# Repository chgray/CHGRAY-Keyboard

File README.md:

https://github.com/freerouting/freerouting

# QMK Tips
./bin/qmk info -km default -kb handwired/ckey

# Graphical view of the keyboard
./bin/qmk info -kb handwired/ckey -l

# Parts
https://kbdfans.com/

# VIA
keyboard layout editor - http://www.keyboard-layout-editor.com/

https://caniusevia.com/docs/specification/

https://get.vial.today/

#QMK PR reqs
The general guide to send PRs to QMK is https://docs.qmk.fm/#/contributing; there is also the PR checklist https://docs.qmk.fm/#/pr_checklist th

qmk c2json -km default -kb handwired/ckey -o foo.json ./keyboards/handwired/ckey/keymaps/default/keymap.c

# To Make the keyplate
	1. in notepad replace Eco.User1 with Edge.Cuts
	2. from pcbnew export the Edge.Cuts layer as a DXF
	3. import this back into pcbnew
	4. Delete all the active components and then manually patch up things

# Parts 
Purchased LED's ffrom https://www.adafruit.com/product/4960

# KiCad
 - to make the file load pcbnew and then do File->Fabrication Outputs.  save a .pos file {CSV, millimeters, seperate files for front/back} -> Generate Position File.  (chgray-keyboard-top-pos.csv)
	A) Change Ref to Designator
	B) Rot to Rotation
	C) Side to Layer
	D) PoxX to "Mid X"
	E) PosY to "Mid Y"
 
 - to make the BOM load eeschema and then do the button ("generate bill of material") BOM -> bom2csv
     you're looking for chgray-keyboard.csv
	A) Change Reference to "Designator"
	B) Change Datasheet to "JLCPCB Part #"
	C) Value to Comment

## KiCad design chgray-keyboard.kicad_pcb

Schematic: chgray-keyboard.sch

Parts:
J1: Conn_01x07_Female; PinHeader_1x08_P2.54mm_Vertical

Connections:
COL12: J1.3; also elsewhere on the board
COL13: J1.4; also elsewhere on the board
LED_DATA: J1.2; also elsewhere on the board
LED_OUT: J1.8; also elsewhere on the board
RESET: J1.6; also elsewhere on the board
ROW0: J1.5; also elsewhere on the board

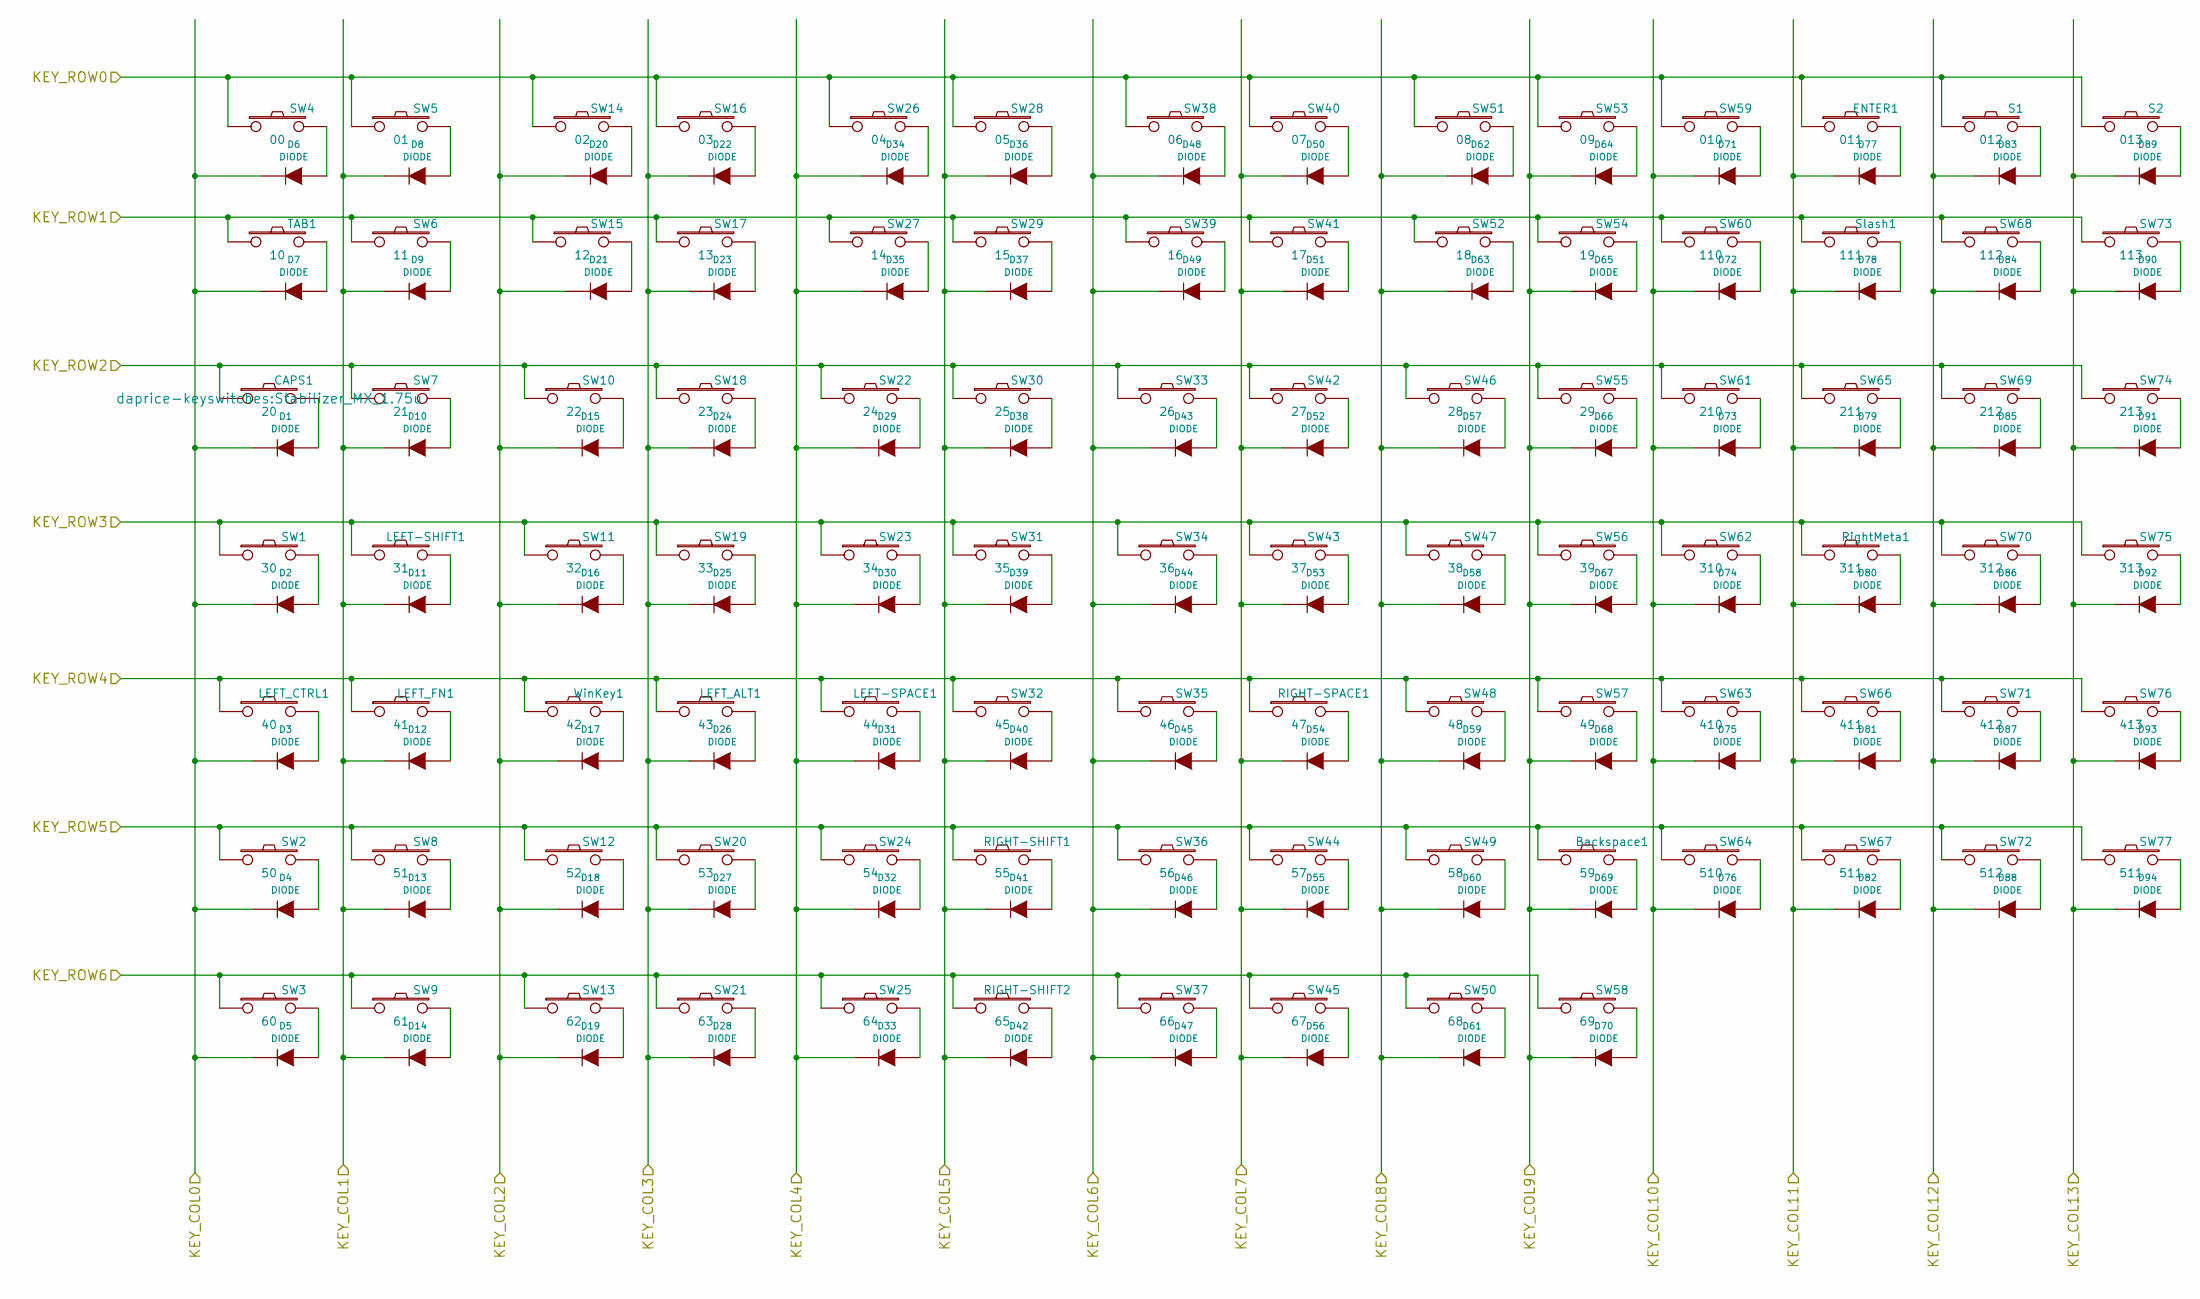
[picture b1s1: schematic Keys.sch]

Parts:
Backspace1: 59; Stabilizer_MX_2u
CAPS1: 20; Stabilizer_MX_1.75u
D1, D2, D3, D4, D5, D6, D7, D8, D9, D10, D11, D12, D13, D14, D15, D16, D17, D18, D19, D20, D21, D22, D23, D24, D25, D26, D27, D28, D29, D30, D31, D32, D33, D34, D35, D36, D37, D38, D39, D40, D41, D42, D43, D44, D45, D46, D47, D48, D49, D50, D51, D52, D53, D54, D55, D56, D57, D58, D59, D60, D61, D62, D63, D64, D65, D66, D67, D68, D69, D70, D71, D72, D73, D74, D75, D76, D77, D78, D79, D80, D81, D82, D83, D84, D85, D86, D87, D88, D89, D90, D91, D92, D93, D94: DIODE; D_SOD-123FL
ENTER1: 011; Stabilizer_MX_2.25u
LEFT-SHIFT1: 31; Stabilizer_MX_2.25u
LEFT-SPACE1: 44; Kailh_socket_MX
LEFT_ALT1: 43; Kailh_socket_MX
LEFT_CTRL1: 40; Stabilizer_MX_1.25u
LEFT_FN1: 41; Stabilizer_MX_1.25u
RIGHT-SHIFT1: 55; Stabilizer_MX_2.75u
RIGHT-SHIFT2: 65; Kailh_socket_MX
RIGHT-SPACE1: 47; Stabilizer_MX_1.25u
RightMeta1: 311; Stabilizer_MX_1.25u
S1: 012; Kailh_socket_MX
S2: 013; Kailh_socket_MX
SW1: 30; Kailh_socket_MX
SW2: 50; Kailh_socket_MX
SW3: 60; Kailh_socket_MX
SW4: 00; Kailh_socket_MX
SW5: 01; Kailh_socket_MX
SW6: 11; Kailh_socket_MX
SW7: 21; Kailh_socket_MX
SW8: 51; Kailh_socket_MX
SW9: 61; Kailh_socket_MX
SW10: 22; Kailh_socket_MX
SW11: 32; Kailh_socket_MX
SW12: 52; Kailh_socket_MX
SW13: 62; Kailh_socket_MX
SW14: 02; Kailh_socket_MX
SW15: 12; Kailh_socket_MX
SW16: 03; Kailh_socket_MX
SW17: 13; Kailh_socket_MX
SW18: 23; Kailh_socket_MX
SW19: 33; Kailh_socket_MX
SW20: 53; Kailh_socket_MX
SW21: 63; Kailh_socket_MX
SW22: 24; Kailh_socket_MX
SW23: 34; Kailh_socket_MX
SW24: 54; Kailh_socket_MX
SW25: 64; Kailh_socket_MX
SW26: 04; Kailh_socket_MX
SW27: 14; Kailh_socket_MX
SW28: 05; Kailh_socket_MX
SW29: 15; Kailh_socket_MX
SW30: 25; Kailh_socket_MX
SW31: 35; Kailh_socket_MX
SW32: 45; Kailh_socket_MX
SW33: 26; Kailh_socket_MX
SW34: 36; Kailh_socket_MX
SW35: 46; Kailh_socket_MX
SW36: 56; Kailh_socket_MX
SW37: 66; Kailh_socket_MX
SW38: 06; Kailh_socket_MX
SW39: 16; Kailh_socket_MX
SW40: 07; Kailh_socket_MX
SW41: 17; Kailh_socket_MX
SW42: 27; Kailh_socket_MX
SW43: 37; Kailh_socket_MX
SW44: 57; Kailh_socket_MX
SW45: 67; Kailh_socket_MX
SW46: 28; Kailh_socket_MX
SW47: 38; Kailh_socket_MX
SW48: 48; Stabilizer_MX_1.25u
SW49: 58; Kailh_socket_MX
SW50: 68; Kailh_socket_MX
SW51: 08; Kailh_socket_MX
SW52: 18; Kailh_socket_MX
SW53: 09; Kailh_socket_MX
SW54: 19; Kailh_socket_MX
SW55: 29; Kailh_socket_MX
SW56: 39; Kailh_socket_MX
SW57: 49; CHERRY_PCB_625H
SW58: 69; Stabilizer_MX_1.25u
SW59: 010; Kailh_socket_MX
SW60: 110; Kailh_socket_MX
SW61: 210; Kailh_socket_MX
SW62: 310; Kailh_socket_MX
SW63: 410; Kailh_socket_MX
SW64: 510; Kailh_socket_MX
SW65: 211; Kailh_socket_MX
SW66: 411; Kailh_socket_MX
SW67, SW77: 511; Kailh_socket_MX
SW68: 112; Kailh_socket_MX
SW69: 212; Kailh_socket_MX
SW70: 312; Kailh_socket_MX
SW71: 412; Kailh_socket_MX
SW72: 512; Kailh_socket_MX
SW73: 113; Kailh_socket_MX
SW74: 213; Kailh_socket_MX
SW75: 313; Kailh_socket_MX
SW76: 413; Kailh_socket_MX
Slash1: 111; Stabilizer_MX_1.5u
TAB1: 10; Stabilizer_MX_1.5u
WinKey1: 42; Stabilizer_MX_1.25u

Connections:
COL0: D1.2 (K), D2.2 (K), D3.2 (K), D4.2 (K), D5.2 (K), D6.2 (K), D7.2 (K); also elsewhere on the board
COL1: D8.2 (K), D9.2 (K), D10.2 (K), D11.2 (K), D12.2 (K), D13.2 (K), D14.2 (K); also elsewhere on the board
COL2: D15.2 (K), D16.2 (K), D17.2 (K), D18.2 (K), D19.2 (K), D20.2 (K), D21.2 (K); also elsewhere on the board
COL3: D22.2 (K), D23.2 (K), D24.2 (K), D25.2 (K), D26.2 (K), D27.2 (K), D28.2 (K); also elsewhere on the board
COL4: D29.2 (K), D30.2 (K), D31.2 (K), D32.2 (K), D33.2 (K), D34.2 (K), D35.2 (K); also elsewhere on the board
COL5: D36.2 (K), D37.2 (K), D38.2 (K), D39.2 (K), D40.2 (K), D41.2 (K), D42.2 (K); also elsewhere on the board
COL6: D43.2 (K), D44.2 (K), D45.2 (K), D46.2 (K), D47.2 (K), D48.2 (K), D49.2 (K); also elsewhere on the board
COL7: D50.2 (K), D51.2 (K), D52.2 (K), D53.2 (K), D54.2 (K), D55.2 (K), D56.2 (K); also elsewhere on the board
COL8: D57.2 (K), D58.2 (K), D59.2 (K), D60.2 (K), D61.2 (K), D62.2 (K), D63.2 (K); also elsewhere on the board
COL9: D64.2 (K), D65.2 (K), D66.2 (K), D67.2 (K), D68.2 (K), D69.2 (K), D70.2 (K); also elsewhere on the board
COL10: D71.2 (K), D72.2 (K), D73.2 (K), D74.2 (K), D75.2 (K), D76.2 (K); also elsewhere on the board
COL11: D77.2 (K), D78.2 (K), D79.2 (K), D80.2 (K), D81.2 (K), D82.2 (K); also elsewhere on the board
COL12: D83.2 (K), D84.2 (K), D85.2 (K), D86.2 (K), D87.2 (K), D88.2 (K); also elsewhere on the board
COL13: D89.2 (K), D90.2 (K), D91.2 (K), D92.2 (K), D93.2 (K), D94.2 (K); also elsewhere on the board
unnamed: Backspace1.2, D69.1 (A)
unnamed: CAPS1.2, D1.1 (A)
unnamed: D2.1 (A), SW1.2
unnamed: D3.1 (A), LEFT_CTRL1.2
unnamed: D4.1 (A), SW2.2
unnamed: D5.1 (A), SW3.2
unnamed: D6.1 (A), SW4.2
unnamed: D7.1 (A), TAB1.2
unnamed: D8.1 (A), SW5.2
unnamed: D9.1 (A), SW6.2
unnamed: D10.1 (A), SW7.2
unnamed: D11.1 (A), LEFT-SHIFT1.2
unnamed: D12.1 (A), LEFT_FN1.2
unnamed: D13.1 (A), SW8.2
unnamed: D14.1 (A), SW9.2
unnamed: D15.1 (A), SW10.2
unnamed: D16.1 (A), SW11.2
unnamed: D17.1 (A), WinKey1.2
unnamed: D18.1 (A), SW12.2
unnamed: D19.1 (A), SW13.2
unnamed: D20.1 (A), SW14.2
unnamed: D21.1 (A), SW15.2
unnamed: D22.1 (A), SW16.2
unnamed: D23.1 (A), SW17.2
unnamed: D24.1 (A), SW18.2
unnamed: D25.1 (A), SW19.2
unnamed: D26.1 (A), LEFT_ALT1.2
unnamed: D27.1 (A), SW20.2
unnamed: D28.1 (A), SW21.2
unnamed: D29.1 (A), SW22.2
unnamed: D30.1 (A), SW23.2
unnamed: D31.1 (A), LEFT-SPACE1.2
unnamed: D32.1 (A), SW24.2
unnamed: D33.1 (A), SW25.2
unnamed: D34.1 (A), SW26.2
unnamed: D35.1 (A), SW27.2
unnamed: D36.1 (A), SW28.2
unnamed: D37.1 (A), SW29.2
unnamed: D38.1 (A), SW30.2
unnamed: D39.1 (A), SW31.2
unnamed: D40.1 (A), SW32.2
unnamed: D41.1 (A), RIGHT-SHIFT1.2
unnamed: D42.1 (A), RIGHT-SHIFT2.2
unnamed: D43.1 (A), SW33.2
unnamed: D44.1 (A), SW34.2
unnamed: D45.1 (A), SW35.2
unnamed: D46.1 (A), SW36.2
unnamed: D47.1 (A), SW37.2
unnamed: D48.1 (A), SW38.2
unnamed: D49.1 (A), SW39.2
unnamed: D50.1 (A), SW40.2
unnamed: D51.1 (A), SW41.2
unnamed: D52.1 (A), SW42.2
unnamed: D53.1 (A), SW43.2
unnamed: D54.1 (A), RIGHT-SPACE1.2
unnamed: D55.1 (A), SW44.2
unnamed: D56.1 (A), SW45.2
unnamed: D57.1 (A), SW46.2
unnamed: D58.1 (A), SW47.2
unnamed: D59.1 (A), SW48.2
unnamed: D60.1 (A), SW49.2
unnamed: D61.1 (A), SW50.2
unnamed: D62.1 (A), SW51.2
unnamed: D63.1 (A), SW52.2
unnamed: D64.1 (A), SW53.2
unnamed: D65.1 (A), SW54.2
unnamed: D66.1 (A), SW55.2
unnamed: D67.1 (A), SW56.2
unnamed: D68.1 (A), SW57.2
unnamed: D70.1 (A), SW58.2
unnamed: D71.1 (A), SW59.2
unnamed: D72.1 (A), SW60.2
unnamed: D73.1 (A), SW61.2
unnamed: D74.1 (A), SW62.2
unnamed: D75.1 (A), SW63.2
unnamed: D76.1 (A), SW64.2
unnamed: D77.1 (A), ENTER1.2
unnamed: D78.1 (A), Slash1.2
unnamed: D79.1 (A), SW65.2
unnamed: D80.1 (A), RightMeta1.2
unnamed: D81.1 (A), SW66.2
unnamed: D82.1 (A), SW67.2
unnamed: D83.1 (A), S1.2
unnamed: D84.1 (A), SW68.2
unnamed: D85.1 (A), SW69.2
unnamed: D86.1 (A), SW70.2
unnamed: D87.1 (A), SW71.2
unnamed: D88.1 (A), SW72.2
unnamed: D89.1 (A), S2.2
unnamed: D90.1 (A), SW73.2
unnamed: D91.1 (A), SW74.2
unnamed: D92.1 (A), SW75.2
unnamed: D93.1 (A), SW76.2
unnamed: D94.1 (A), SW77.2
ROW0: ENTER1.1, S1.1, S2.1, SW4.1, SW5.1, SW14.1, SW16.1, SW26.1, SW28.1, SW38.1, SW40.1, SW51.1, SW53.1, SW59.1; also elsewhere on the board
ROW1: SW6.1, SW15.1, SW17.1, SW27.1, SW29.1, SW39.1, SW41.1, SW52.1, SW54.1, SW60.1, SW68.1, SW73.1, Slash1.1, TAB1.1; also elsewhere on the board
ROW2: CAPS1.1, SW7.1, SW10.1, SW18.1, SW22.1, SW30.1, SW33.1, SW42.1, SW46.1, SW55.1, SW61.1, SW65.1, SW69.1, SW74.1; also elsewhere on the board
ROW3: LEFT-SHIFT1.1, RightMeta1.1, SW1.1, SW11.1, SW19.1, SW23.1, SW31.1, SW34.1, SW43.1, SW47.1, SW56.1, SW62.1, SW70.1, SW75.1; also elsewhere on the board
ROW4: LEFT-SPACE1.1, LEFT_ALT1.1, LEFT_CTRL1.1, LEFT_FN1.1, RIGHT-SPACE1.1, SW32.1, SW35.1, SW48.1, SW57.1, SW63.1, SW66.1, SW71.1, SW76.1, WinKey1.1; also elsewhere on the board
ROW5: Backspace1.1, RIGHT-SHIFT1.1, SW2.1, SW8.1, SW12.1, SW20.1, SW24.1, SW36.1, SW44.1, SW49.1, SW64.1, SW67.1, SW72.1, SW77.1; also elsewhere on the board
ROW6: RIGHT-SHIFT2.1, SW3.1, SW9.1, SW13.1, SW21.1, SW25.1, SW37.1, SW45.1, SW50.1, SW58.1; also elsewhere on the board

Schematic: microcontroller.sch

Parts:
C102, C103, C104, C105: 0.1u; C_0805_2012Metric
C106: 10u; C_0805_2012Metric
C107, C108: 22p; C_0805_2012Metric
C109: 1u; C_0805_2012Metric
J2: USB_B_Mini; USB_Mini-B_Wuerth_65100516121_Horizontal
R1, R4: R10k; R_1206_3216Metric
R2, R3: 22R; R_0805_2012Metric
SW_RESET1: SW_Push; SW_SPST_JLC_PCB_C520860
U1: ATmega32U4-MU; QFN-44-1EP_7x7mm_P0.5mm_EP5.2x5.2mm
Y1: Crystal; JLC_PCB_C111377

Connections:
/ATmega32U4-AU/PC6: U1.31
/ATmega32U4-AU/PF0: U1.41
/ATmega32U4-AU/PF1: U1.40
COL0: U1.27; also elsewhere on the board
COL1: U1.26; also elsewhere on the board
COL2: U1.22; also elsewhere on the board
COL3: U1.25; also elsewhere on the board
COL4: U1.21; also elsewhere on the board
COL5: U1.20; also elsewhere on the board
COL6: U1.19; also elsewhere on the board
COL7: U1.18; also elsewhere on the board
COL8: U1.12; also elsewhere on the board
COL9: U1.30; also elsewhere on the board
COL10: U1.29; also elsewhere on the board
COL11: U1.28; also elsewhere on the board
COL12: U1.11; also elsewhere on the board
COL13: U1.10; also elsewhere on the board
LED_DATA: U1.1; also elsewhere on the board
unnamed: C107.1, U1.17, Y1.1
unnamed: C108.1, U1.16, Y1.2
unnamed: C109.2, U1.6
unnamed: J2.2, R3.2
unnamed: J2.3, R2.2
unnamed: R2.1, U1.4
unnamed: R3.1, U1.3
unnamed: R4.2, U1.33
RESET: R1.2, SW_RESET1.2, U1.13; also elsewhere on the board
ROW0: U1.9; also elsewhere on the board
ROW1: U1.8; also elsewhere on the board
ROW2: U1.36; also elsewhere on the board
ROW3: U1.37; also elsewhere on the board
ROW4: U1.38; also elsewhere on the board
ROW5: U1.39; also elsewhere on the board
ROW6: U1.32; also elsewhere on the board

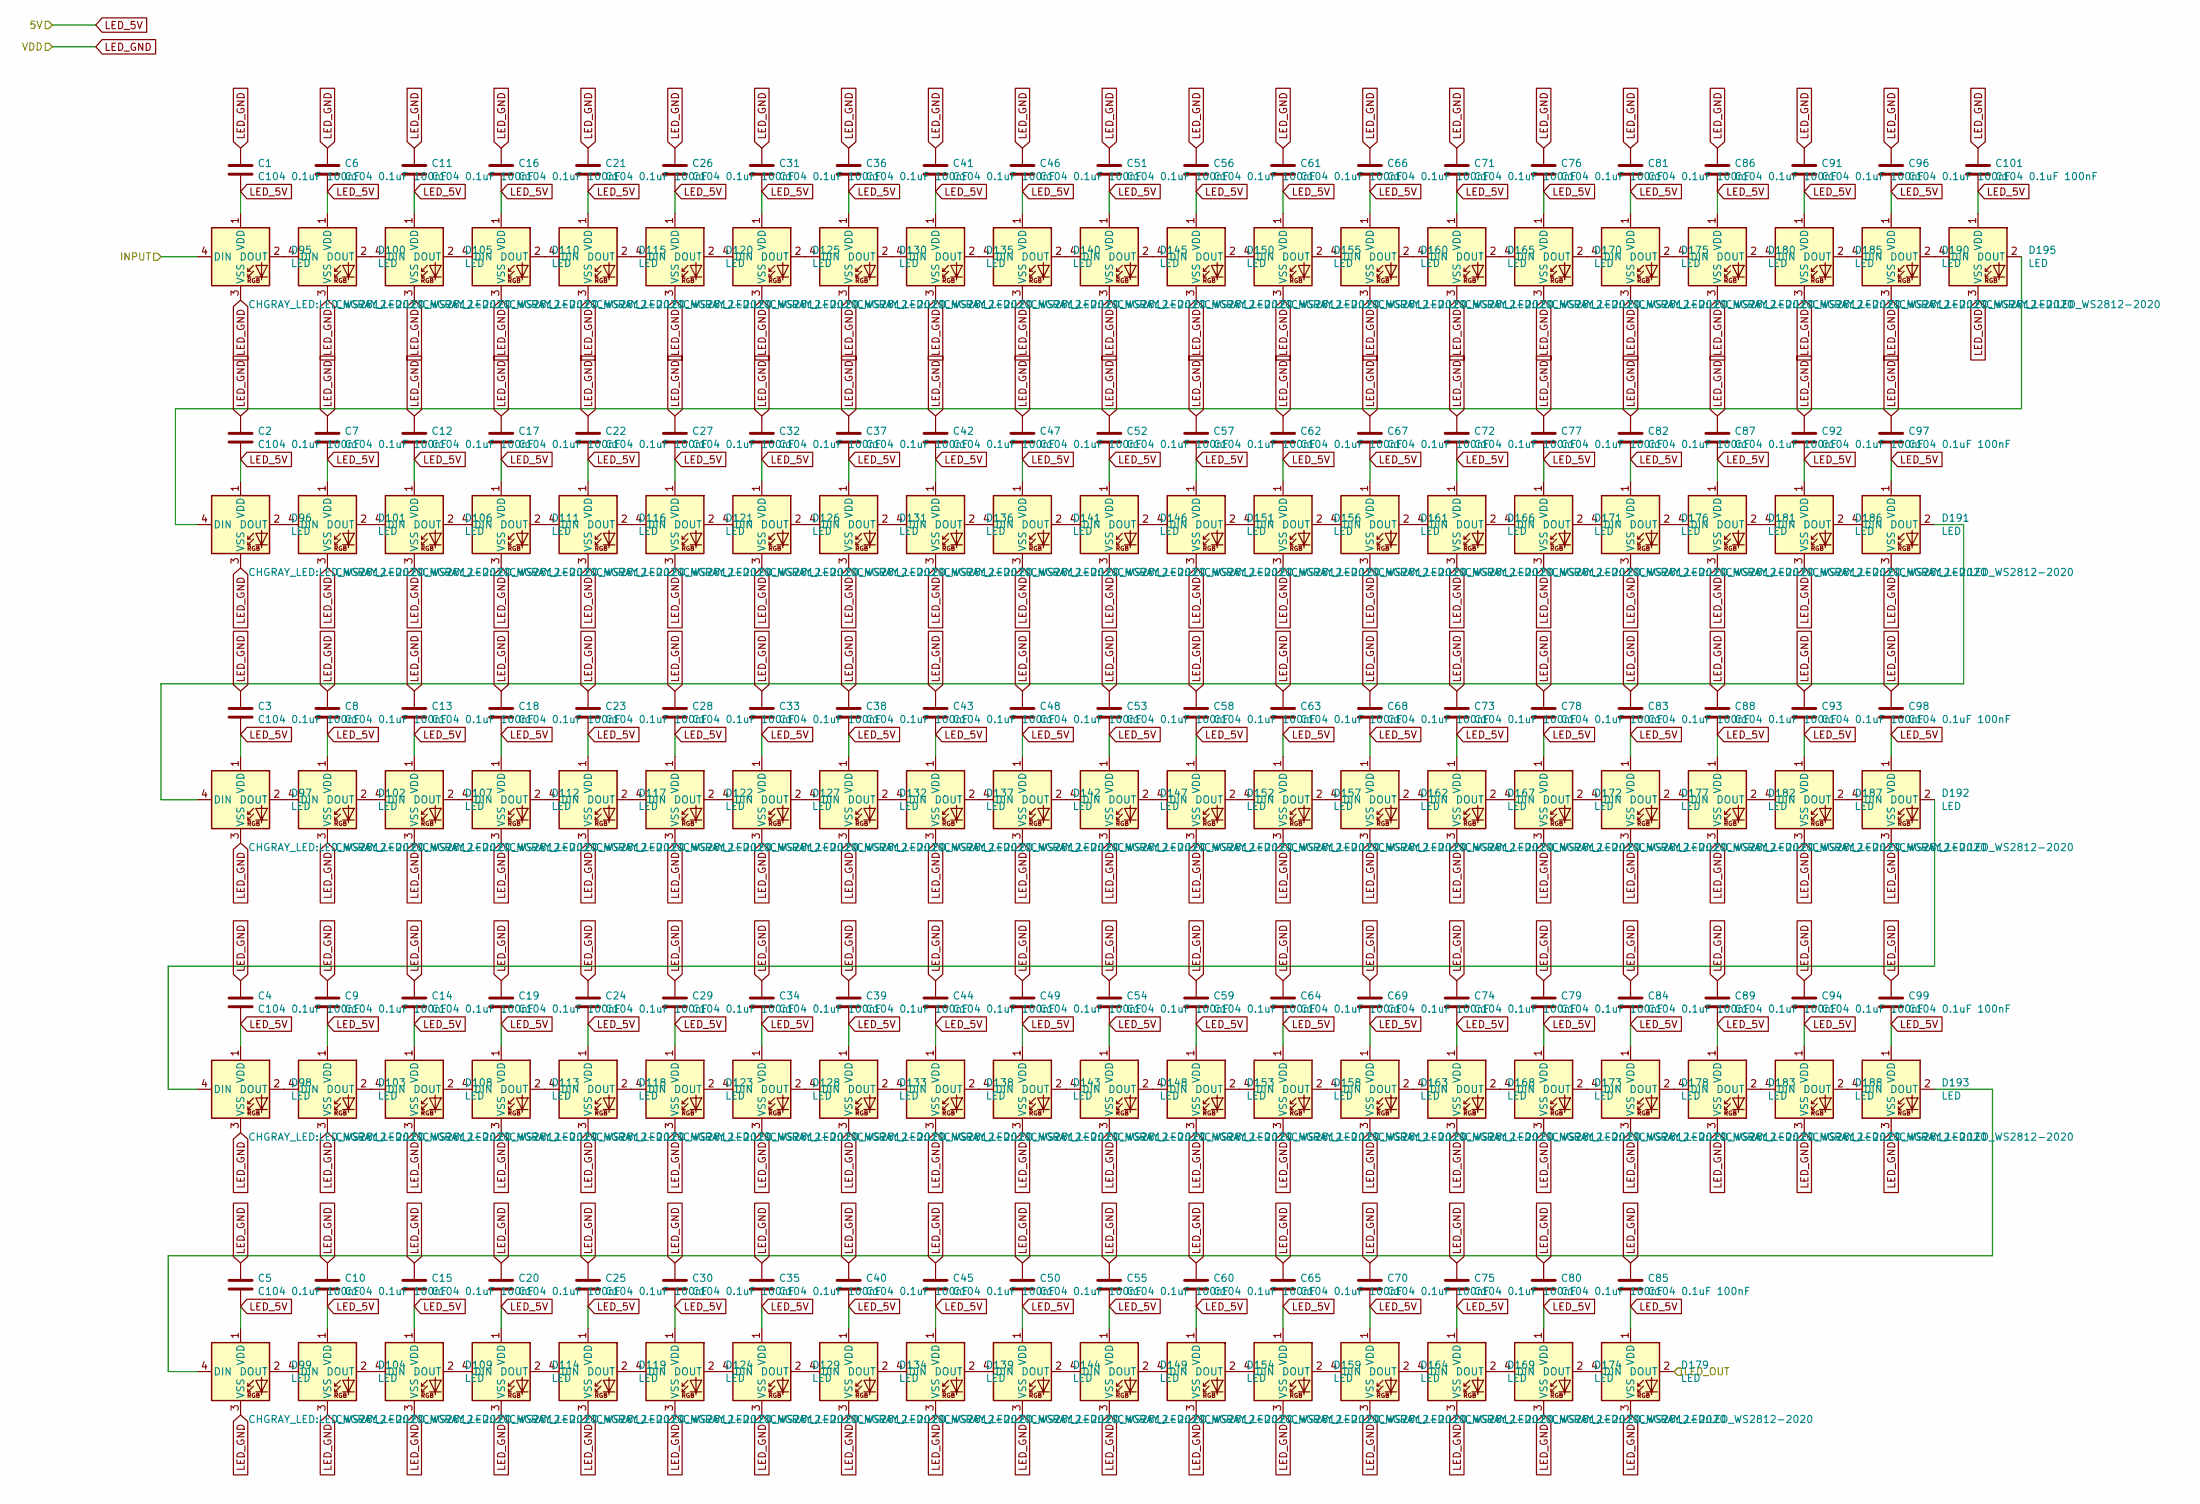
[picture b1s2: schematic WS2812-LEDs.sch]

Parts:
C1, C2, C3, C4, C5, C6, C7, C8, C9, C10, C11, C12, C13, C14, C15, C16, C17, C18, C19, C20, C21, C22, C23, C24, C25, C26, C27, C28, C29, C30, C31, C32, C33, C34, C35, C36, C37, C38, C39, C40, C41, C42, C43, C44, C45, C46, C47, C48, C49, C50, C51, C52, C53, C54, C55, C56, C57, C58, C59, C60, C61, C62, C63, C64, C65, C66, C67, C68, C69, C70, C71, C72, C73, C74, C75, C76, C77, C78, C79, C80, C81, C82, C83, C84, C85, C86, C87, C88, C89, C91, C92, C93, C94, C96, C97, C98, C99, C101: C104 0.1uF 100nF; C_0402_1005Metric
D95, D96, D97, D98, D99, D100, D101, D102, D103, D104, D105, D106, D107, D108, D109, D110, D111, D112, D113, D114, D115, D116, D117, D118, D119, D120, D121, D122, D123, D124, D125, D126, D127, D128, D129, D130, D131, D132, D133, D134, D135, D136, D137, D138, D139, D140, D141, D142, D143, D144, D145, D146, D147, D148, D149, D150, D151, D152, D153, D154, D155, D156, D157, D158, D159, D160, D161, D162, D163, D164, D165, D166, D167, D168, D169, D170, D171, D172, D173, D174, D175, D176, D177, D178, D179, D180, D181, D182, D183, D185, D186, D187, D188, D190, D191, D192, D193, D195: LED; LED_WS2812-2020

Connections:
LED_DATA: D95.4 (DIN); also elsewhere on the board
LED_OUT: D179.2 (DOUT); also elsewhere on the board
unnamed: D100.2 (DOUT), D105.4 (DIN)
unnamed: D95.2 (DOUT), D100.4 (DIN)
unnamed: D101.2 (DOUT), D106.4 (DIN)
unnamed: D96.2 (DOUT), D101.4 (DIN)
unnamed: D102.2 (DOUT), D107.4 (DIN)
unnamed: D97.2 (DOUT), D102.4 (DIN)
unnamed: D103.2 (DOUT), D108.4 (DIN)
unnamed: D98.2 (DOUT), D103.4 (DIN)
unnamed: D104.2 (DOUT), D109.4 (DIN)
unnamed: D99.2 (DOUT), D104.4 (DIN)
unnamed: D105.2 (DOUT), D110.4 (DIN)
unnamed: D106.2 (DOUT), D111.4 (DIN)
unnamed: D107.2 (DOUT), D112.4 (DIN)
unnamed: D108.2 (DOUT), D113.4 (DIN)
unnamed: D109.2 (DOUT), D114.4 (DIN)
unnamed: D110.2 (DOUT), D115.4 (DIN)
unnamed: D111.2 (DOUT), D116.4 (DIN)
unnamed: D112.2 (DOUT), D117.4 (DIN)
unnamed: D113.2 (DOUT), D118.4 (DIN)
unnamed: D114.2 (DOUT), D119.4 (DIN)
unnamed: D115.2 (DOUT), D120.4 (DIN)
unnamed: D116.2 (DOUT), D121.4 (DIN)
unnamed: D117.2 (DOUT), D122.4 (DIN)
unnamed: D118.2 (DOUT), D123.4 (DIN)
unnamed: D119.2 (DOUT), D124.4 (DIN)
unnamed: D120.2 (DOUT), D125.4 (DIN)
unnamed: D121.2 (DOUT), D126.4 (DIN)
unnamed: D122.2 (DOUT), D127.4 (DIN)
unnamed: D123.2 (DOUT), D128.4 (DIN)
unnamed: D124.2 (DOUT), D129.4 (DIN)
unnamed: D125.2 (DOUT), D130.4 (DIN)
unnamed: D126.2 (DOUT), D131.4 (DIN)
unnamed: D127.2 (DOUT), D132.4 (DIN)
unnamed: D128.2 (DOUT), D133.4 (DIN)
unnamed: D129.2 (DOUT), D134.4 (DIN)
unnamed: D130.2 (DOUT), D135.4 (DIN)
unnamed: D131.2 (DOUT), D136.4 (DIN)
unnamed: D132.2 (DOUT), D137.4 (DIN)
unnamed: D133.2 (DOUT), D138.4 (DIN)
unnamed: D134.2 (DOUT), D139.4 (DIN)
unnamed: D135.2 (DOUT), D140.4 (DIN)
unnamed: D136.2 (DOUT), D141.4 (DIN)
unnamed: D137.2 (DOUT), D142.4 (DIN)
unnamed: D138.2 (DOUT), D143.4 (DIN)
unnamed: D139.2 (DOUT), D144.4 (DIN)
unnamed: D140.2 (DOUT), D145.4 (DIN)
unnamed: D141.2 (DOUT), D146.4 (DIN)
unnamed: D142.2 (DOUT), D147.4 (DIN)
unnamed: D143.2 (DOUT), D148.4 (DIN)
unnamed: D144.2 (DOUT), D149.4 (DIN)
unnamed: D145.2 (DOUT), D150.4 (DIN)
unnamed: D146.2 (DOUT), D151.4 (DIN)
unnamed: D147.2 (DOUT), D152.4 (DIN)
unnamed: D148.2 (DOUT), D153.4 (DIN)
unnamed: D149.2 (DOUT), D154.4 (DIN)
unnamed: D150.2 (DOUT), D155.4 (DIN)
unnamed: D151.2 (DOUT), D156.4 (DIN)
unnamed: D152.2 (DOUT), D157.4 (DIN)
unnamed: D153.2 (DOUT), D158.4 (DIN)
unnamed: D154.2 (DOUT), D159.4 (DIN)
unnamed: D155.2 (DOUT), D160.4 (DIN)
unnamed: D156.2 (DOUT), D161.4 (DIN)
unnamed: D157.2 (DOUT), D162.4 (DIN)
unnamed: D158.2 (DOUT), D163.4 (DIN)
unnamed: D159.2 (DOUT), D164.4 (DIN)
unnamed: D160.2 (DOUT), D165.4 (DIN)
unnamed: D161.2 (DOUT), D166.4 (DIN)
unnamed: D162.2 (DOUT), D167.4 (DIN)
unnamed: D163.2 (DOUT), D168.4 (DIN)
unnamed: D164.2 (DOUT), D169.4 (DIN)
unnamed: D165.2 (DOUT), D170.4 (DIN)
unnamed: D166.2 (DOUT), D171.4 (DIN)
unnamed: D167.2 (DOUT), D172.4 (DIN)
unnamed: D168.2 (DOUT), D173.4 (DIN)
unnamed: D169.2 (DOUT), D174.4 (DIN)
unnamed: D170.2 (DOUT), D175.4 (DIN)
unnamed: D171.2 (DOUT), D176.4 (DIN)
unnamed: D172.2 (DOUT), D177.4 (DIN)
unnamed: D173.2 (DOUT), D178.4 (DIN)
unnamed: D174.2 (DOUT), D179.4 (DIN)
unnamed: D175.2 (DOUT), D180.4 (DIN)
unnamed: D176.2 (DOUT), D181.4 (DIN)
unnamed: D177.2 (DOUT), D182.4 (DIN)
unnamed: D178.2 (DOUT), D183.4 (DIN)
unnamed: D180.2 (DOUT), D185.4 (DIN)
unnamed: D181.2 (DOUT), D186.4 (DIN)
unnamed: D182.2 (DOUT), D187.4 (DIN)
unnamed: D183.2 (DOUT), D188.4 (DIN)
unnamed: D185.2 (DOUT), D190.4 (DIN)
unnamed: D186.2 (DOUT), D191.4 (DIN)
unnamed: D187.2 (DOUT), D192.4 (DIN)
unnamed: D188.2 (DOUT), D193.4 (DIN)
unnamed: D190.2 (DOUT), D195.4 (DIN)
unnamed: D97.4 (DIN), D191.2 (DOUT)
unnamed: D98.4 (DIN), D192.2 (DOUT)
unnamed: D99.4 (DIN), D193.2 (DOUT)
unnamed: D96.4 (DIN), D195.2 (DOUT)

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
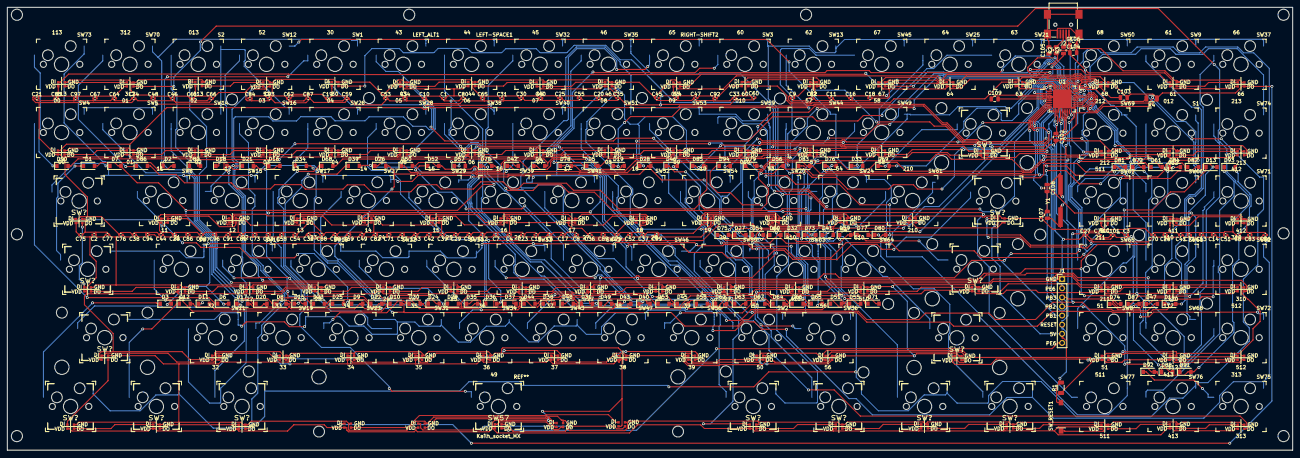
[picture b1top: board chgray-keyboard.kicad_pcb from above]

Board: 2 copper layers, 358.3 x 123.4 mm, 401 parts (0 on the bottom side), 225 nets.

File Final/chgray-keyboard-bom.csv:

Designator,Footprint,Quantity,Designation,LCSC
"D84,D83,D82,D81,D80,D79,D78,D77,D76,D75,D74,D73,D72,D71,D70,D69,D68,D67,D66,D65,D64,D63,D62,D61,D60,D59,D58,D57,D56,D55,D54,D53,D52,D51,D50,D49,D48,D47,D46,D45,D44,D43,D42,D41,D40,D39,D38,D37,D36,D35,D34,D33,D32,D31,D30,D29,D28,D27,D26,D25,D24,D23,D22,D21,D20,D19,D18,D17,D16,D15,D14,D13,D12,D11,D10,D9,D8,D7,D6,D5,D4,D3,D2,D1",D_SOD-123,84,DIODE,C129828
SW_RESET1,SW_SPST_JLC_PCB_C520860,1,SW_Push,C520860
Y1-16hz1,Crystal_SMD_HC49-SD,1,Crystal,C12676
J2,USB_Mini-B_Wuerth_65100516121_Horizontal,1,USB_B_Mini,C69074
"D168,D167,D166,D165,D164,D163,D162,D161,D160,D159,D158,D157,D156,D155,D154,D153,D152,D151,D150,D149,D148,D147,D146,D145,D144,D143,D142,D141,D140,D139,D138,D137,D136,D135,D134,D133,D132,D131,D130,D129,D128,D127,D126,D125,D124,D123,D122,D121,D120,D119,D118,D117,D116,D115,D114,D113,D112,D111,D110,D109,D108,D107,D106,D105,D104,D103,D102,D101,D100,D99,D98,D97,D96,D95,D94,D93,D92,D91,D90,D89,D88,D87,D86,D85",LED_WS2812-2020,84,LED,C965555
"C90,C91",C_0805_2012Metric,2,22p,C1804
"R3,R2",R_0805_2012Metric,2,22R,C17561
C92,C_0805_2012Metric,1,1u,C28323
"C89,C88,C87,C86,C85",C_0805_2012Metric,5,0.1u,C696366
"R4,R1",R_1206_3216Metric,2,R10k,C17902
U1,TQFP-44_10x10mm_P0.8mm,1,ATmega32U4-AU,C44854
J1,PinHeader_2x07_P1.27mm_Vertical,1,Conn_01x01_Female,
"C3,C5,C6,C8,C9,C11,C13,C16,C17,C18,C21,C23,C25,C27,C28,C29,C30,C32,C33,C35,C36,C37,C40,C41,C42,C43,C44,C47,C48,C49,C50,C52,C53,C54,C55,C56,C57,C60,C62,C63,C67,C68,C69,C70,C71,C74,C75,C76,C78,C80,C81,C82,C84,C22,C24,C26,C15,C20,C19,C39,C34,C45,C31,C38,C46,C51,C66,C72,C77,C83,C73,C64,C79,C65,C59,C58,C61,C4,C7,C10,C14,C2,C12,C1",C_0402_1005Metric,84,C104  0.1uF 100nF,C1525

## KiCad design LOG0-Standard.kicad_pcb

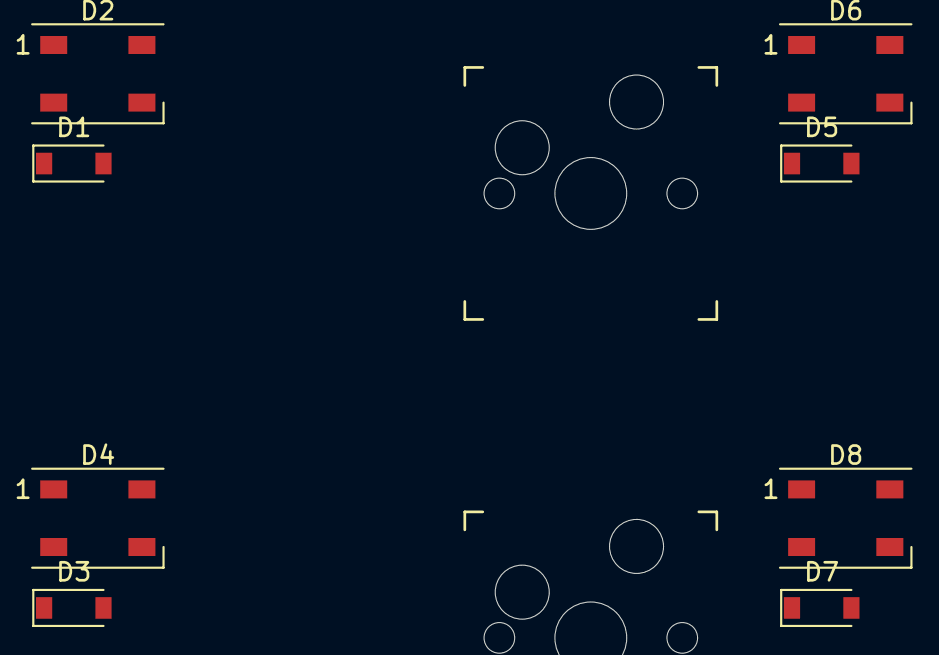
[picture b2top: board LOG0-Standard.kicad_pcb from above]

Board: 2 copper layers, 12 parts (0 on the bottom side), 4 nets, no tracks yet.

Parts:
D1, D3, D5, D7: DIODE; D_SOD-123
D2, D4, D6, D8: WS2812B; LED_WS2812B_PLCC4_5.0x5.0mm_P3.2mm
SW1, SW2, SW3, SW4: SWITCH_PUSH; Kailh_socket_MX

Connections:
unnamed: D1.1, SW1.2
unnamed: D3.1, SW2.2
unnamed: D5.1, SW3.2
unnamed: D7.1, SW4.2

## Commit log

2017-02-04 Starting spot, added submodules
    -Cherry footprints from (https://github.com/BathroomEpiphanies/KiCAD-Keyboard-Tutorial.git)
    -Teensy footprints from (https://github.com/XenGi/kicad_teensy.git)
2017-02-04 renaming project
2017-02-04 Created Part for NXP PCA9532 BS
    http://www.nxp.com/products/interfaces/ic-bus-portfolio/ic-led-display-control/16-bit-i2c-bus-led-dimmer:PCA9532BS?tab=Documentation_Tab
2017-02-04 placing parts
2017-02-05 completing iteration with the LED's
2017-02-11 test keyboard
2017-02-13 footprint
2021-02-13 keyboard
2021-02-13 update submodules
2021-03-02 messing around
2021-03-02 submodules
2021-03-02 working
2021-03-02 update modules
2021-03-06 docker file
2021-03-07 working on docker
2021-03-07 dockers
2021-03-07 keyboard.ino
2021-03-20 file
2021-03-20 add cherry submodule
2021-03-20 experiment
2021-03-30 fiddling
2021-03-31 print as sent for pcb:1
2021-04-09 readme
2021-04-17 might work...
2021-04-23 add daprice keyswitches
2021-04-23 removing unused things
2021-04-23 flip to daprice pads
2021-04-23 add 1U bounding box
2021-04-25 laying out the keys with logan
2021-04-25 fix submodule
2021-04-25 iterating
2021-04-28 remove cache
2021-04-28 add 1.75U switch
2021-05-04 keys
2021-05-08 prob a bad idea
2021-05-08 Revert "working"
    This reverts commit 5a6b199d0bddcd61efb91924755a1876b79ec0a1.
2021-05-08 fiddling with RGB
2021-05-08 RGB experiment
2021-05-08 working on rgb
2021-05-08 2.25u stabalized
2021-05-09 laying out keyboard, for final mfg
2021-05-09 laying out keyboard; all keys aligned!
2021-05-09 Squashed commit of the following:
    commit 82315f0ae1d56e508510c236d094091e5279ecfb
    Author: Chris Gray (COSINE FUNDAMENTALS) <chgray@microsoft.com>
    Date: Sun May 9 12:30:08 2021 -0700
    remove pdf
    commit 9829b40eb261ee4368c12e62176b20d48804d4ea
    Author: Chris Gray (COSINE FUNDAMENTALS) <chgray@microsoft.com>
2021-05-09 almost done
2021-05-09 placed LED's ..mostly
2021-05-10 routed
2021-05-13 Logan signed off on board location
2021-05-14 n-1 to sendoff
2021-05-15 remove files that shouldnt have been checked in
2021-05-15 cleaning up absolute paths
2021-05-15 remove cached items that shouldnt be here
2021-05-15 remove unused filep
2021-05-21 adding microcontroller
2021-05-21 working on the chip
2021-05-21 working on microcontrller
2021-05-21 update keys not to include rescue
2021-05-27 fix labels
2021-06-03 RGB circuit rescue cleanup
2021-06-03 update keyboard
2021-06-04 updates to be nearly functional
2021-06-07 moving parts around, trying to align to a standard keyboard keycap sizes
2021-06-07 seperate SK6812 and WS2812
2021-06-07 flip to WS2812
2021-06-09 led work
2021-06-09 working on led
2021-06-10 working on the WS2812
2021-06-10 working on layouts
2021-06-10 working on layout
2021-06-10 almost ready to send off
2021-06-10 leds
2021-06-10 trying to clean up diodes
2021-06-10 about to send off
2021-06-11 iterating due to LED's not showing up
2021-06-11 sent off
2021-06-11 final
2021-06-11 unsaved files
2021-06-12 fix leds
2021-06-12 about to send off - take 2
2021-06-12 bom ok
2021-06-13 sent the 2.5 off to JLCPcb!
2021-08-13 dont know
2021-09-01 finished yeet 2.5
2021-09-01 update to Logans new layout
2021-09-07 Yeet 3.0
2021-09-07 clean up silk screens
2021-09-07 add forgotten layers
2021-09-10 files
2021-09-10 problems with files
2021-09-20 sent to jlcpcb
2021-09-22 update labels for row/col scan alignment
2021-09-23 key maps
2021-09-25 change footprints
2021-09-26 working on layouts and plastics
2021-09-26 update module
2021-10-05 keyboard stuff
2021-10-05 working on cad
2021-10-06 swapping out controller with a different one
2021-10-06 attempt at Yeet3.1
2021-10-06 sent to JLCPCB - worked first trip
2021-10-11 stuff
2021-10-25 cutattempt
2021-10-25 removnig some bad ideas from the PCB
2021-10-26 add plate
2021-11-05 working on mappings
2021-11-05 working on switch widths
2021-11-11 almost done with the 3.3
2021-11-11 working on 6.3
2021-11-11 gerber files
2021-11-11 would be okay but JLCPCB is out of the chip
2021-11-15 3.3-AU
2021-11-16 update to new keyboard sizes
2021-11-17 attempting 3.3-AU
2021-12-07 working on Yeet3.4; changed microcontroller, added screw hole, and I think fixed the 5V LED issue (needs to be verified)
2021-12-12 almost done; routing
2021-12-12 add LED pin to breakouts
2021-12-12 cleaning up
2021-12-13 Yeet; possibly final!!
2022-01-02 flipped Eco1.User to Edge.Cuts
2022-01-02 keyplate
2022-01-02 final keyplate
2022-01-02 backplate finished
2022-03-22 working on USB-C
2022-07-12 copy the ATMega32U4-AU into our private library
2023-07-08 Final/l0gan co/l0 key yeet3.4 (#2)
    * renaming project
    * Created Part for NXP PCA9532 BS
    http://www.nxp.com/products/interfaces/ic-bus-portfolio/ic-led-display-control/16-bit-i2c-bus-led-dimmer:PCA9532BS?tab=Documentation_Tab
    * placing parts
    * completing iteration with the LED's
    * test keyboard
